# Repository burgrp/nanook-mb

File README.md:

# NANOOK main control board

Nanook-mb is control board for open source [NANOOK ground-water heat pump](https://cad.onshape.com/documents/2a5990c1c14b1713fdde9141/w/393a2c463278bded31251c68/e/64a137d08251e156e9e96024?explodedView=MXEOv0Y8%2BFJTUT8HV&renderMode=0&rightPanel=explodedViewPanel&uiState=64dd1223bc9e520fdb3377e3) project. The board is responsible for:

- soft-switching three phases compressor
- switching two circulation pumps
- controlling Carel Electronic Expansion Valve
- reading
  - safety low and high pressure switches
  - water temperature sensors on all exchanger ports (eight sensors in total)
  - water pressure sensors on cold and hot side
  - water flow sensors on cold and hot side
  - refrigerant pressure sensors on cold and hot side
- providing configuration web user interface via WiFi connection

## Safety warnings
TBD: grounding, connectors, switching (rocker vs. ext. CB)

## System connections

### Diagram

### Wiring

#### Mains to MB (#1)
Connection to mains is done by flexible cable 5x 2.5mm<sup>2</sup>. Mains side should be connected to on-wall box with dedicated circuit breaker (3x16A). Board side end must be terminated with insulated Faston 6.3 connectors and connected to L1, L2, L3 and N terminals of the board. To avoid contact with metal chassis, use angled Fastons only.

Ground wire must be terminated by crimp eye-type connector and mounted by screw to chassis.

### MB to compressor (#2)
This is, with #1, another high-current connection done by 3x 2.5mm<sup>2</sup> cable. Both sides must be terminated by 6.3 Fastons.

### MB to PWM SSR power lines (#3, #4)
These are six 2.5mm<sup>2</sup> wires terminated by 6.3 Fastons on board side and by eye on SSR side. Make sure all six wires (R, S, T, U, V, W) are connected to properly.

### MB to ON/OFF switch (#5)
There is a rocker switch to turn heat pump ON and OFF. The switch just disconnects onboard power supply, which in turn opens onboard coil relays. This means that the board is still powered even with the rocker switch turned off.

### MB to PWM SSR control lines (#6, #7)
These lines connects main board and PWM SSR control circuit. Two lines supply the control circuit with 230V AC power (#6). The other two are control signal 0-5V. Leave SSR contacts 4-20mA and +5V unconnected.

### MB to circulation pumps (#8, #9)
The main board directly controls primary (cold) and secondary (hot) side circulation pumps. Onboard SSRs are rated to 100W max power output.

### MB to safety pressure switches (#10, #11)
Connections to safety pressure switches on low pressure and high pressure sides.

### MB to electronic expansion valve (#12)
For wires of EEV stepper motor. Color coding for Carel valves is marked on PCB:
- GN - green
- BN - brown
- WE - white
- YW - yellow.

### I<sup>2</sup>C bus (#13)
There are three connectors on board, all of them sharing single I<sup>2</sup>C bus. Analog sensor boards are connected by 6-wire flat cable with crimped Micro-Match connectors.

There may be two separate cables for each analog sensors board, or there may be single cable shared by both analog sensors boards.

### Analog sensors board to temperature sensors (#14, #15, #16, #17, #24, #25, #26, #27)
Temperatures are measured by NTC 10K 1% 3950 thermistors.

There are waterproof thermistors with JST-XH connectors available. They may be used directly with no additional crimping needed.

Thermistors should be tightly mounted on appropriate pipes, ideally with thermal conductive paste and outer environment insulation cover.

Thermistors are located as follows:
- #14: "cold side refrigerant output" - evaporator refrigerant output to compressor suction
- #15: "cold side refrigerant input" - EEV to evaporator refrigerant input
- #16: "cold side water output" - evaporator water output to collector input
- #17: "cold side water input" - collector output to evaporator water input
- #24: "hot side water input" - cold water from heating system to condenser water input
- #25: "hot side water output" - hot water from condenser to heating system
- #26: "hot side refrigerant input" - compressor discharge to condenser refrigerant input
- #27: "hot side refrigerant output" - condenser refrigerant output to EEV or refrigerant accumulator

### Analog sensors board to pressure sensors (#18, #19, #22, #23)
Pressure sensors are available either with other connectors than JST-XH or with no connector at all. You need to crimp proper three wire JST-XH connectors as:

- 1: GND (black)
- 2: SIGNAL (yellow)
- 3: +5V (red)

and for Carel sensors with green, white and black wires as:

- 1: GND (green)
- 2: SIGNAL (white)
- 3: +5V (black)

Pressure sensors are located as follows:
- #18: "cold side refrigerant pressure" - compressor suction, -1...9,3bar => 0...5V, recommended SPKT0013RO
- #19: "cold side water pressure" - collector water loop, 0...1.2MPa => 0...5V
- #22: "hot side water pressure" - heating system water loop, 0...1.2MPa => 0...5V
- #23: "hot side refrigerant pressure" - compressor discharge, 0...34,5bar => 0...5V, recommended SPKT0033RO

Ultisolar water pressure sensor 0...1.2MPa

Carel SPKT refrigerant pressure sensor

### Analog sensors board to water flow sensors (#20, #21)
Water flow sensors are available either with other connectors than JST-XH or with no connector at all. You need to crimp proper three wire JST-XH connectors as
- 1: GND (black)
- 2: SIGNAL (yellow)
- 3: +5V (red)

Water sensors are located as follows:
- #20: "cold side water flow" - collector water loop
- #21: "hot side water flow" - heating system water loop

USC-HS10TA BSP is a suitable water flow sensor

### MB to WiFi antenna (#28)

Main board is connected to network by WiFi. Although there is small chip antenna integrated on board, an external antenna is needed because of metal enclosure. Connect a 2.4GHz antenna by IPEX connector.

## Compiling firmware
In order to compile and flash firmware, you need to install Node.js, openocd and arm-none-eabi GCC.

Source code is written our [Silicon build system](https://github.com/device-farm/silicon).
Install Silicon by:
```sh
sudo npm install -g @device.farm/silicon
```

And then build and flash by:
```sh
silicon build -dsf
```

The `-f` parameter instructs Silicon to flash the image using openocd, which should be connected to your MCU and listening on port 4444.

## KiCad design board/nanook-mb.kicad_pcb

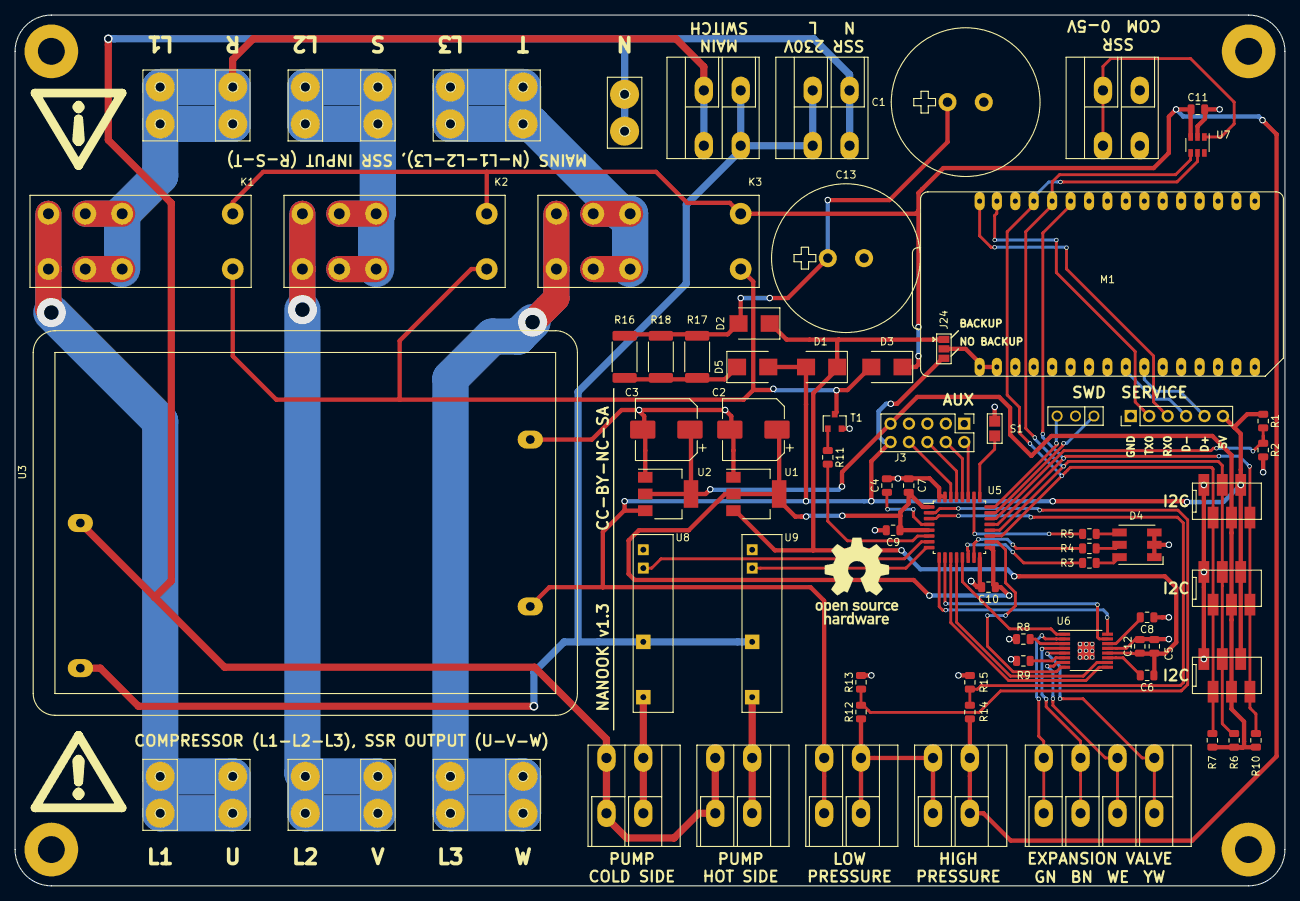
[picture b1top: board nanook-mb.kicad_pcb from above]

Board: 2 copper layers, 175.0 x 120.0 mm, 78 parts (0 on the bottom side), 64 nets.

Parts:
C1, C13: 2F; BCE005R5C205FS
C2, C3: 1m; CP_Elec_8x10
C4, C7, C9, C10, C11, C12: 100n; C_0805_2012Metric
C5: 10u; C_0805_2012Metric
C6: 10n; C_0805_2012Metric
C8: 2.2M; C_0805_2012Metric
D1, D2, D3, D5: SK22; D_SMB
D4: LED_RGB; LED_RGB_5050-6
J1: Power Switch; DG142R-2-5.08
J2: Mains L1; Tab-6.3
J3: AUX; PinHeader_2x05_P2.54mm_Vertical
J4: E2V; DG142R-4-5.08
J5: LPS; DG142R-2-5.08
J6: Pump Cold Side; DG142R-2-5.08
J7: Pump Hot Side; DG142R-2-5.08
J8: HPS; DG142R-2-5.08
J9: Mains L2; Tab-6.3
J10: Service; PinHeader_1x06_P2.54mm_Vertical
J11: Mains L3; Tab-6.3
J12: Mains N; Tab-6.3
J13: SSR 220; DG142R-2-5.08
J14: SSR 0-5V; DG142R-2-5.08
J15: Compressor L1; Tab-6.3
J16: Compressor L2; Tab-6.3
J17: Compressor L3; Tab-6.3
J18: SSR Output L1; Tab-6.3
J19: SSR Output L2; Tab-6.3
J20: SSR Output L3; Tab-6.3
J21: SSR Input L1; Tab-6.3
J22: SSR Input L2; Tab-6.3
J23: SSR Input L3; Tab-6.3
J24: GS3; SolderJumper-3_P1.3mm_Open_Pad1.0x1.5mm
K1, K2, K3: RELAY_2; RT314_Relay
M1: NanoPi-Duo
R1, R2, R6, R7, R10, R12, R13, R14, R15: 4k7; R_0805_2012Metric
R3, R4, R5: 270R; R_0805_2012Metric
R8, R9: 0R22; R_0805_2012Metric
R11: 1K5; R_0805_2012Metric
R16, R17, R18: 4R7/2W; R_2512_6332Metric
S1: SB2P
T1: BC817; SOT-23
U1, U2: NCP1117-3.3_SOT223; SOT-223-3_TabPin2
U3: Mean Well PM-15-5; Mean-Well-PM-15-5
U5: STM32F030K6Tx; LQFP-32_7x7mm_P0.8mm
U6: DRV8833; TSSOP-16_4.4x5mm_Pitch0.65mm-EP
U7: MCP4706A0T-E/CH; SOT-23-6
U8, U9: G3MB-5V-SSR; G3MB-SSR
X1: SWD
X2: I2C Cold Side; Micro-Match-FOB-6
X3: I2C Hot Side; Micro-Match-FOB-6
X4: I2C Aux; Micro-Match-FOB-6

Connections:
+3V3: C3.1, J3.9, R6.1, R7.1, R10.1, U2.2, X2.4, X3.4, X4.4
+5V: D1.2, D5.2, J3.10, J5.1, J10.6, J24.3, R1.1, U2.3, U3.4, X2.5, X3.5, X4.5
/3V3_BACKUP: C2.1, C7.1, C9.1, C10.1, U1.2, U5.1, U5.5, U5.17
/5V_BACKUP: C5.2, C6.1, C12.1, D1.1, D2.1, J24.1, U1.3, U6.12
/ALERT: M1.22, R10.2, U5.21, X2.6, X3.6, X4.6
/BACKUP_C: C1.1, C13.1, D2.2, R16.1, R17.1, R18.1
/COMP_5V: C11.1, D3.1, J8.2, K1.A1, K2.A1, K3.A1, R14.1, U7.3
/COMP_L1: J15.1, J18.1, K1.14, K1.24
/COMP_L2: J16.1, J19.1, K2.14, K2.24
/COMP_L3: J17.1, J20.1, K3.14, K3.24
/COMP_RAMP: J14.2, U7.1
/COMP_RELAY: R11.2, U5.6
/COMP_RELAY_PWR: D3.2, K1.A2, K2.A2, K3.A2, T1.3
/E2V_A1: U5.9, U6.16
/E2V_A2: U5.10, U6.15
/E2V_B1: U5.11, U6.9
/E2V_B2: U5.12, U6.10
/E2V_NFAULT: U5.18, U6.8
/E2V_NSLEEP: U5.13, U6.1
/HPS: R14.2, R15.1, U5.3
/LPS: R12.2, R13.1, U5.2
/MAINS_L1: J1.2, J2.1, J21.1, K1.11, K1.12, K1.21, K1.22
/MAINS_L2: J9.1, J22.1, K2.11, K2.12, K2.21, K2.22
/MAINS_L3: J11.1, J23.1, K3.11, K3.12, K3.21, K3.22
/MAINS_N: J6.1, J7.1, J12.1, J13.1, U3.2
/PUMP_COLD_SIDE: U5.7, U8.3
/PUMP_HOT_SIDE: U5.8, U9.3
/PWR_OK: R1.2, R2.1, U5.22
/RX0: J10.3, M1.17
/SCL: M1.20, R7.2, U5.19, U7.5, X2.2, X3.2, X4.2
/SDA: M1.21, R6.2, U5.20, U7.4, X2.3, X3.3, X4.3
/SWCLK: U5.24, X1.3
/SWDIO: U5.23, X1.1
/SWITCHED_L: J1.1, J13.2, U3.1, U8.2, U9.2
/TX0: J10.2, M1.18
/USB-DM: J10.4, M1.8
/USB-DP: J10.5, M1.7
GND: C1.2, C2.2, C3.2, C4.2, C5.1, C7.2, C8.1, C9.2, C10.2, C11.2, C12.2, C13.2, D4.1, D4.2, D4.3, J3.1, J3.3, J3.5, J3.7, J10.1, J14.1, M1.13, M1.19, R2.2, R8.1, R9.1, R13.2, R15.2, S1.2, T1.2, U1.1, U2.1, U3.3, U5.16, U5.31, U5.32, U6.13, U6.17, U7.2, U8.4, U9.4, X1.2, X2.1, X3.1, X4.1
unnamed: C4.1, U5.4
unnamed: C6.2, U6.11
unnamed: C8.2, U6.14
unnamed: D4.4, R5.2
unnamed: D4.5, R4.2
unnamed: D4.6, R3.2
unnamed: D5.1, R16.2, R17.2, R18.2
unnamed: J3.2, U5.27
unnamed: J3.4, U5.28
unnamed: J3.6, U5.29
unnamed: J3.8, U5.30
unnamed: J4.1, U6.2
unnamed: J4.2, U6.4
unnamed: J4.3, U6.7
unnamed: J4.4, U6.5
unnamed: J5.2, J8.1, R12.1
unnamed: J6.2, U8.1
unnamed: J7.2, U9.1
unnamed: J24.2, M1.15, M1.16
unnamed: R3.1, U5.14
unnamed: R4.1, U5.15
unnamed: R5.1, U5.26
unnamed: R8.2, U6.3
unnamed: R9.2, U6.6
unnamed: R11.1, T1.1
unnamed: S1.1, U5.25

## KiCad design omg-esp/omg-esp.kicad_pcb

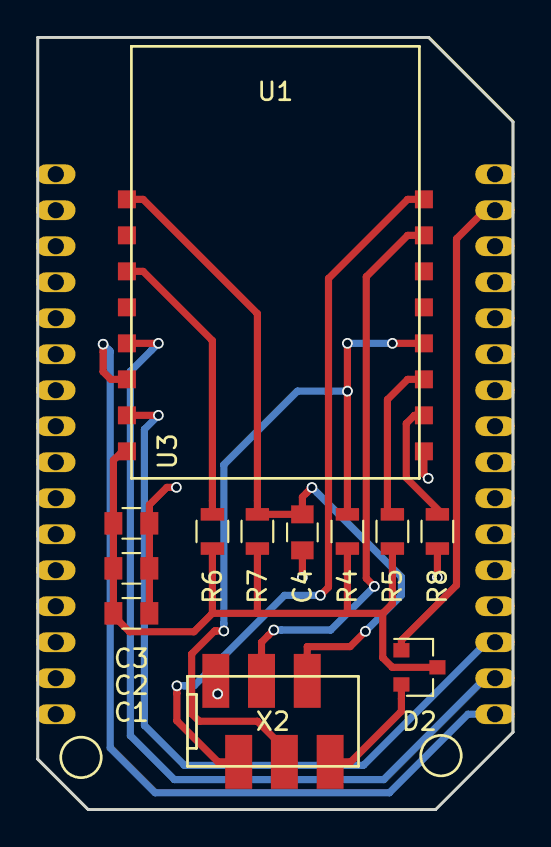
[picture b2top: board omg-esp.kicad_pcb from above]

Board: 2 copper layers, 26.4 x 42.9 mm, 13 parts (0 on the bottom side), 14 nets.

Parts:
C1, C2: 47u; C_0805
C3, C4: 100n; C_0805
D2: BAT54C; SOT-23
R4, R5, R6, R7, R8: 10k; R_0805
U1: Omega2; Omega2+
U3: ESP-12
X2: ESP-PROG; Micro-Match-FOB-6

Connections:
+3V3: D2.1, U1.31
/ALERT: U1.19, U3.7
/ESP/3V3-PROG: D2.2, X2.6
/ESP/3V3_ESP: C1.1, C2.1, C3.1, D2.3, R4.2, R5.2, R6.2, R7.2, U3.8
/ESP/EN: R6.1, U3.3
/ESP/GPIO0: R4.1, U3.12, X2.4
/ESP/GPIO2: R5.1, U3.11
/ESP/GPIO15: R8.1, U3.10
/ESP/RESET: C4.2, R7.1, U3.1, X2.5
/ESP/RX: U3.15, X2.3
/ESP/TX: U3.16, X2.2
/SCL: U1.18, U3.5
/SDA: U1.17, U3.6
GND: C1.2, C2.2, C3.2, C4.1, R8.2, U1.1, U1.32, U3.9, X2.1

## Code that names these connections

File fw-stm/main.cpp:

const int VALUE_UNKNOWN = -1;

enum Command {
	CMD_NONE,
	CMD_I2C_SET_RGB_LED,
	CMD_RUN_EEV,
	CMD_SET_OUTPUT
};

const int outputPinsCount = 3;
const int inputPinsCount = 5;

const int pwrOkPin = 12;

class GWHP: public i2c::hw::BufferedSlave {

	struct __attribute__ ((packed)) {
		unsigned char command;
		union {
			rgbLed::Setting rgbLed;
			struct __attribute__ ((packed)) {
				short fullSteps;
				unsigned char fast;
			} runEev;
			struct __attribute__ ((packed)) {
				unsigned char outputIndex;
				unsigned char state;
			} setOutput;

		};
	} i2cRxBuffer;

	struct __attribute__ ((packed)) {
		unsigned char outputs;
		unsigned char inputs;
		int eevPosition;
	} i2cTxBuffer;

    rgbLed::Setting rgbSettings[2] = {{
		// power down 
        .rampUpTime = 50,
        .onTime = 0,
        .rampDownTime = 50,
        .offTime = 100,
        .rgb = { 0, 30, 255 }
	},{ 
		// power up
        .rampUpTime = 100,
        .onTime = 0,
        .rampDownTime = 1,
        .offTime = 10,
        .rgb = { 0, 255, 30 }
	}};


public:

	iwdg::Driver iwdg;

	rgbLed::Driver rgbLed;
	eev::Driver eev;

	outputPin::Driver outputPins[outputPinsCount];
	inputPin::Driver inputPins[inputPinsCount];

	inputPin::Driver* pwrOk;

	void init(int i2cAddress) {

		iwdg.init();

		outputPins[0].init(&target::GPIOA, 0, 0); // compressor relay
		outputPins[1].init(&target::GPIOA, 1, 0); // pump cold side
		outputPins[2].init(&target::GPIOA, 2, 0); // pump hot side

		inputPins[0].init(&target::GPIOA, 8, true, false); // EEV NFAULT
		inputPins[1].init(&target::GPIOA, 11, true, false); // I2C ALERT
		inputPins[2].init(&target::GPIOA, pwrOkPin, false, true); pwrOk = &inputPins[2]; // PWR OK		
		inputPins[3].init((volatile target::gpio_a::Peripheral*)&target::GPIOF, 0, false, true); // LPS
		inputPins[4].init((volatile target::gpio_a::Peripheral*)&target::GPIOF, 1, false, true); // HPS

		// EEV
		eev.init(&target::GPIOA, 3, 4, 5, 6, 7, &target::TIM17);

		bool isPwrOk = pwrOk->get();

		// RGB LED
		rgbLed.init(&target::GPIOB, 3, 1, 0, &target::TIM16, &rgbSettings[isPwrOk]);

		if (isPwrOk) {

			// I2C
			target::GPIOA.AFRH.setAFRH(9, 4);
			target::GPIOA.AFRH.setAFRH(10, 4);
			target::GPIOA.MODER.setMODER(9, 2);
			target::GPIOA.MODER.setMODER(10, 2);
			BufferedSlave::init(&target::I2C1, i2cAddress, (unsigned char*)&i2cRxBuffer, sizeof(i2cRxBuffer), (unsigned char*)&i2cTxBuffer, sizeof(i2cTxBuffer));

		} 

		eev.run(500, true);
	}

	virtual void onTxStart() {				                
		i2cTxBuffer.outputs = 0;
		for (int c = 0; c < outputPinsCount; c++) {
			i2cTxBuffer.outputs |= outputPins[c].get() << c;
		}
		i2cTxBuffer.inputs = 0;
		for (int c = 0; c < inputPinsCount; c++) {
			i2cTxBuffer.inputs |= inputPins[c].get() << c;
		}
		i2cTxBuffer.eevPosition = eev.getPosition();
	}

	virtual void onStop(bool read) {
		if (!read) {
			Command command = (Command) i2cRxBuffer.command;
			i2cRxBuffer.command = CMD_NONE;
			switch (command) {
				case CMD_I2C_SET_RGB_LED: {
					rgbLed.set(&i2cRxBuffer.rgbLed);
					break;
				}
				case CMD_RUN_EEV: {
					eev.run(i2cRxBuffer.runEev.fullSteps, i2cRxBuffer.runEev.fast);
					break;
				}
				case CMD_SET_OUTPUT: {
					if (i2cRxBuffer.setOutput.outputIndex < outputPinsCount) {
						outputPins[i2cRxBuffer.setOutput.outputIndex].set(i2cRxBuffer.setOutput.state);
					}					
					break;
				}
			}
		}
	}

	void handlePwrOkInterrupt() {		
		if (target::EXTI.PR.getPR(pwrOkPin)) {
			// reboot on both edges, no need to clear interrupt
			iwdg.reboot();
		}
	}

};

GWHP gwhp;

void interruptHandlerI2C1() {
	gwhp.handleInterrupt();
}

void interruptHandlerTIM16() {
	gwhp.rgbLed.handleInterrupt();
}

void interruptHandlerTIM17() {
	gwhp.eev.handleInterrupt();
}

void interruptHandlerEXTI4_15() {
	gwhp.handlePwrOkInterrupt();
}

void initApplication() {

	target::RCC.AHBENR.setIOPAEN(true);
	target::RCC.AHBENR.setIOPBEN(true);
	target::RCC.AHBENR.setIOPFEN(true);
	target::RCC.APB1ENR.setC_EN(1, 1);
	target::RCC.APB2ENR.setTIM16EN(1);
	target::RCC.APB2ENR.setTIM17EN(1);

	target::NVIC.ISER.setSETENA(1 << target::interrupts::External::I2C1);
	target::NVIC.ISER.setSETENA(1 << target::interrupts::External::TIM16);
	target::NVIC.ISER.setSETENA(1 << target::interrupts::External::TIM17);
	target::NVIC.ISER.setSETENA(1 << target::interrupts::External::EXTI4_15);

	target::SYSCFG.EXTICR4.setEXTI(pwrOkPin, 0);
	target::EXTI.IMR.setMR(pwrOkPin, 1);
	target::EXTI.FTSR.setTR(pwrOkPin, 1);
	target::EXTI.RTSR.setTR(pwrOkPin, 1);

	gwhp.init(0x74);

}

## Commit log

2019-03-11 Kicad 5

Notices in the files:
board/nanook-mb.kicad_pcb:
CC-BY-NC-SA
